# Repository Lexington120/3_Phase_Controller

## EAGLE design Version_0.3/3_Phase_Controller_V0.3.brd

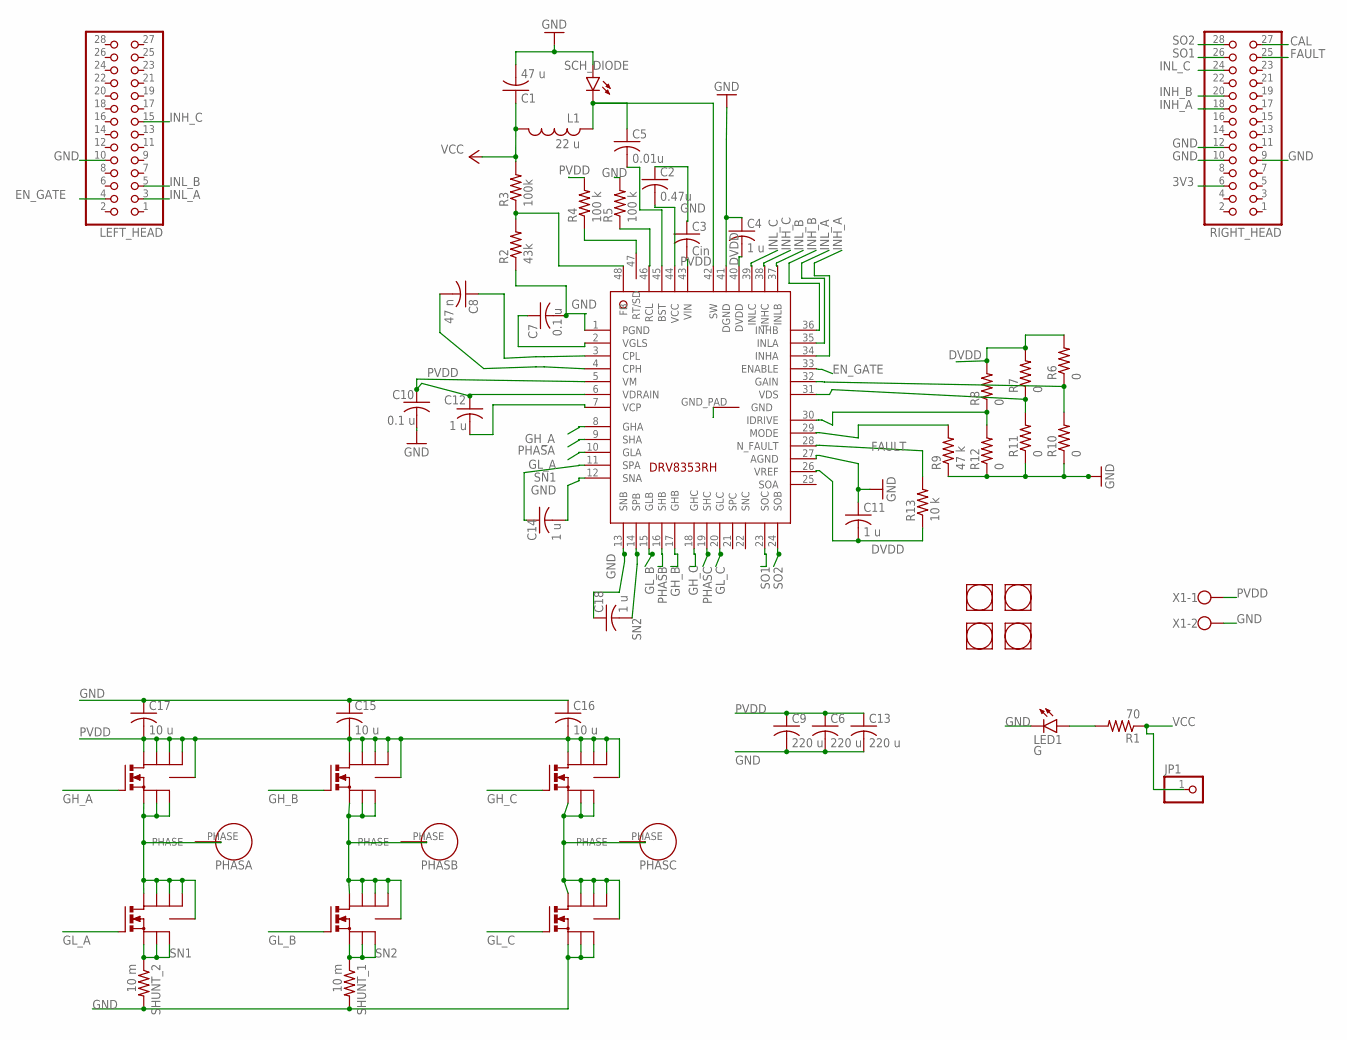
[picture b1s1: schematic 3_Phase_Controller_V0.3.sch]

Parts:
A_H: SIR178DP; POWERPAK_SO-8_SINGLE
A_L: SIR178DP; POWERPAK_SO-8_SINGLE
B_H: SIR178DP; POWERPAK_SO-8_SINGLE
B_L: SIR178DP; POWERPAK_SO-8_SINGLE
C1: 47 u; C025-024X044
C2: 0.47u; C0805
C3: Cin; C0805
C4, C11, C12, C14, C18: 1 u; C0805
C5: 0.01u; C0805
C6, C9, C13: 220 u; C050-045X075
C7, C10: 0.1 u; C0805
C8: 47 n; C0805
C15, C16, C17: 10 u; C1206
C_H: SIR178DP; POWERPAK_SO-8_SINGLE
C_L: SIR178DP; POWERPAK_SO-8_SINGLE
JP1: PINHD-1X1; 1X01
L1: 22 u; L3225M
LED1: G; SML0805
LEFT_HEAD: PINHD-2X14; 2X14
PHASE_A: PHASE_HOLE_V_0.2; HOLE_V_0.2
PHASE_B: PHASE_HOLE_V_0.2; HOLE_V_0.2
PHASE_C: PHASE_HOLE_V_0.2; HOLE_V_0.2
R1: 70; R0805
R2: 43k; R0603
R3: 100k; R0603
R4, R5: 100 k; R0805
R6, R7, R8, R10, R11, R12: 0; R0603
R9: 47 k; R0603
R13: 10 k; R0603
RIGHT_HEAD: PINHD-2X14; 2X14
SCH_DIODE: LEDCHIP-LED0805; CHIP-LED0805
SHUNT_1, SHUNT_2: 10 m; R2512
U$1, U$2, U$4, U$5: STANDOFF
U$3: DRV8353RH; VQFN-RGZ0048A
X1: W237-102

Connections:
3V3: RIGHT_HEAD.6
CAL: RIGHT_HEAD.27
DVDD: C4.2, C11.2, R6.2, R7.2, R8.2, R13.1, U$3.26 (VREF), U$3.40 (DVDD)
EN_GATE: LEFT_HEAD.4, U$3.33 (ENABLE)
FAULT: R13.2, RIGHT_HEAD.25, U$3.28 (N_FAULT)
GH_A: A_H.GATE (G), U$3.8 (GHA)
GH_B: B_H.GATE (G), U$3.17 (GHB)
GH_C: C_H.GATE (G), U$3.18 (GHC)
GL_A: A_L.GATE (G), U$3.10 (GLA)
GL_B: B_L.GATE (G), U$3.15 (GLB)
GL_C: C_L.GATE (G), U$3.20 (GLC)
GND: C1.2, C2.1, C3.1, C4.1, C6.2, C7.2, C9.2, C10.2, C11.1, C13.2, C14.2, C15.1, C16.1, C17.1, C18.1, C_L.S_1 (S), C_L.S_2 (S1), C_L.S_3 (S2), LED1.C, LEFT_HEAD.10, R2.1, R5.2, R9.1, R10.1, R11.1, R12.1, RIGHT_HEAD.9, RIGHT_HEAD.10, RIGHT_HEAD.12, SCH_DIODE.A, SHUNT_1.2, SHUNT_2.2, U$3.1 (PGND), U$3.12 (SNA), U$3.13 (SNB), U$3.27 (AGND), U$3.41 (DGND), U$3.GND_PAD (GND), X1.2
INH_A: RIGHT_HEAD.18, U$3.34 (INHA)
INH_B: RIGHT_HEAD.20, U$3.36 (INHB)
INH_C: LEFT_HEAD.15, U$3.38 (INHC)
INL_A: LEFT_HEAD.3, U$3.35 (INLA)
INL_B: LEFT_HEAD.5, U$3.37 (INLB)
INL_C: RIGHT_HEAD.24, U$3.39 (INLC)
unnamed: LED1.A, R1.2
unnamed: R6.1, R10.2, U$3.32 (GAIN)
unnamed: R2.2, R3.1, U$3.48 (FB)
unnamed: R7.1, R11.2, U$3.31 (VDS)
unnamed: C5.2, U$3.45 (BST)
unnamed: R8.1, R12.2, U$3.30 (IDRIVE)
unnamed: R9.2, U$3.29 (MODE)
unnamed: C2.2, U$3.44 (VCC)
unnamed: C12.2, U$3.7 (VCP)
unnamed: C7.1, U$3.2 (VGLS)
unnamed: R5.1, U$3.46 (RCL)
unnamed: R4.1, U$3.47 (RT/SD)
unnamed: C5.1, L1.2, SCH_DIODE.C, U$3.42 (SW)
unnamed: C8.2, U$3.4 (CPH)
unnamed: C8.1, U$3.3 (CPL)
PHASA: A_H.S_1 (S), A_H.S_2 (S1), A_H.S_3 (S2), A_L.D_1 (D), A_L.D_2 (D1), A_L.D_3 (D2), A_L.D_4 (D3), A_L.THRM (THERMAL), PHASE_A.PHASE, U$3.9 (SHA)
PHASB: B_H.S_1 (S), B_H.S_2 (S1), B_H.S_3 (S2), B_L.D_1 (D), B_L.D_2 (D1), B_L.D_3 (D2), B_L.D_4 (D3), B_L.THRM (THERMAL), PHASE_B.PHASE, U$3.16 (SHB)
PHASC: C_H.S_1 (S), C_H.S_2 (S1), C_H.S_3 (S2), C_L.D_1 (D), C_L.D_2 (D1), C_L.D_3 (D2), C_L.D_4 (D3), C_L.THRM (THERMAL), PHASE_C.PHASE, U$3.19 (SHC)
PVDD: A_H.D_1 (D), A_H.D_2 (D1), A_H.D_3 (D2), A_H.D_4 (D3), A_H.THRM (THERMAL), B_H.D_1 (D), B_H.D_2 (D1), B_H.D_3 (D2), B_H.D_4 (D3), B_H.THRM (THERMAL), C3.2, C6.1, C9.1, C10.1, C12.1, C13.1, C15.2, C16.2, C17.2, C_H.D_1 (D), C_H.D_2 (D1), C_H.D_3 (D2), C_H.D_4 (D3), C_H.THRM (THERMAL), R4.2, U$3.5 (VM), U$3.6 (VDRAIN), U$3.43 (VIN), X1.1
SN1: A_L.S_1 (S), A_L.S_2 (S1), A_L.S_3 (S2), C14.1, SHUNT_2.1, U$3.11 (SPA)
SN2: B_L.S_1 (S), B_L.S_2 (S1), B_L.S_3 (S2), C18.2, SHUNT_1.1, U$3.14 (SPB)
SO1: RIGHT_HEAD.26, U$3.23 (SOC)
SO2: RIGHT_HEAD.28, U$3.24 (SOB)
VCC: C1.1, JP1.1, L1.1, R1.1, R3.2

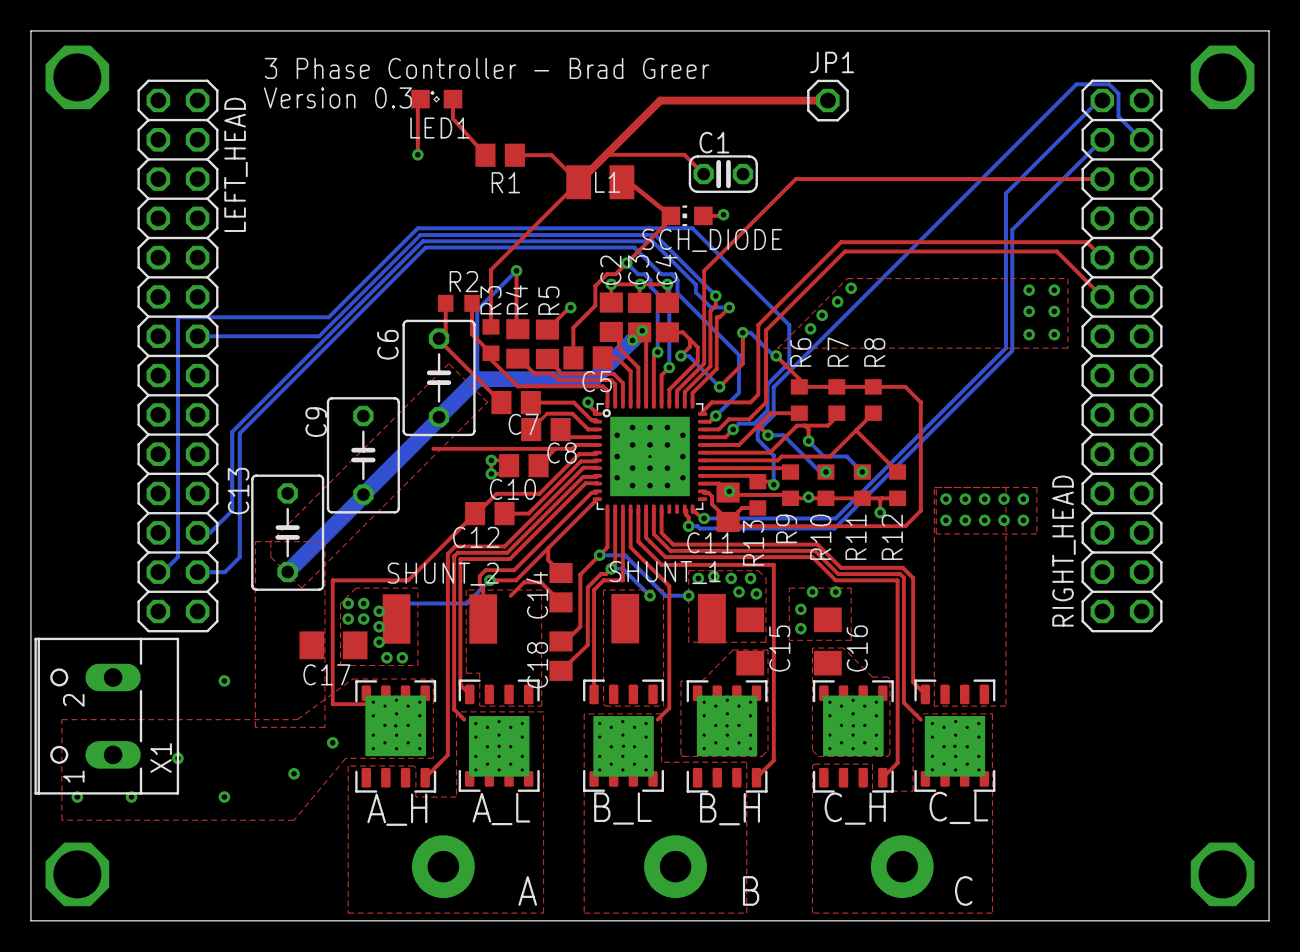
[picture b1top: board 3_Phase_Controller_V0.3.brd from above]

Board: 2 copper layers, 80.0 x 57.5 mm, 54 parts (0 on the bottom side), 40 nets.

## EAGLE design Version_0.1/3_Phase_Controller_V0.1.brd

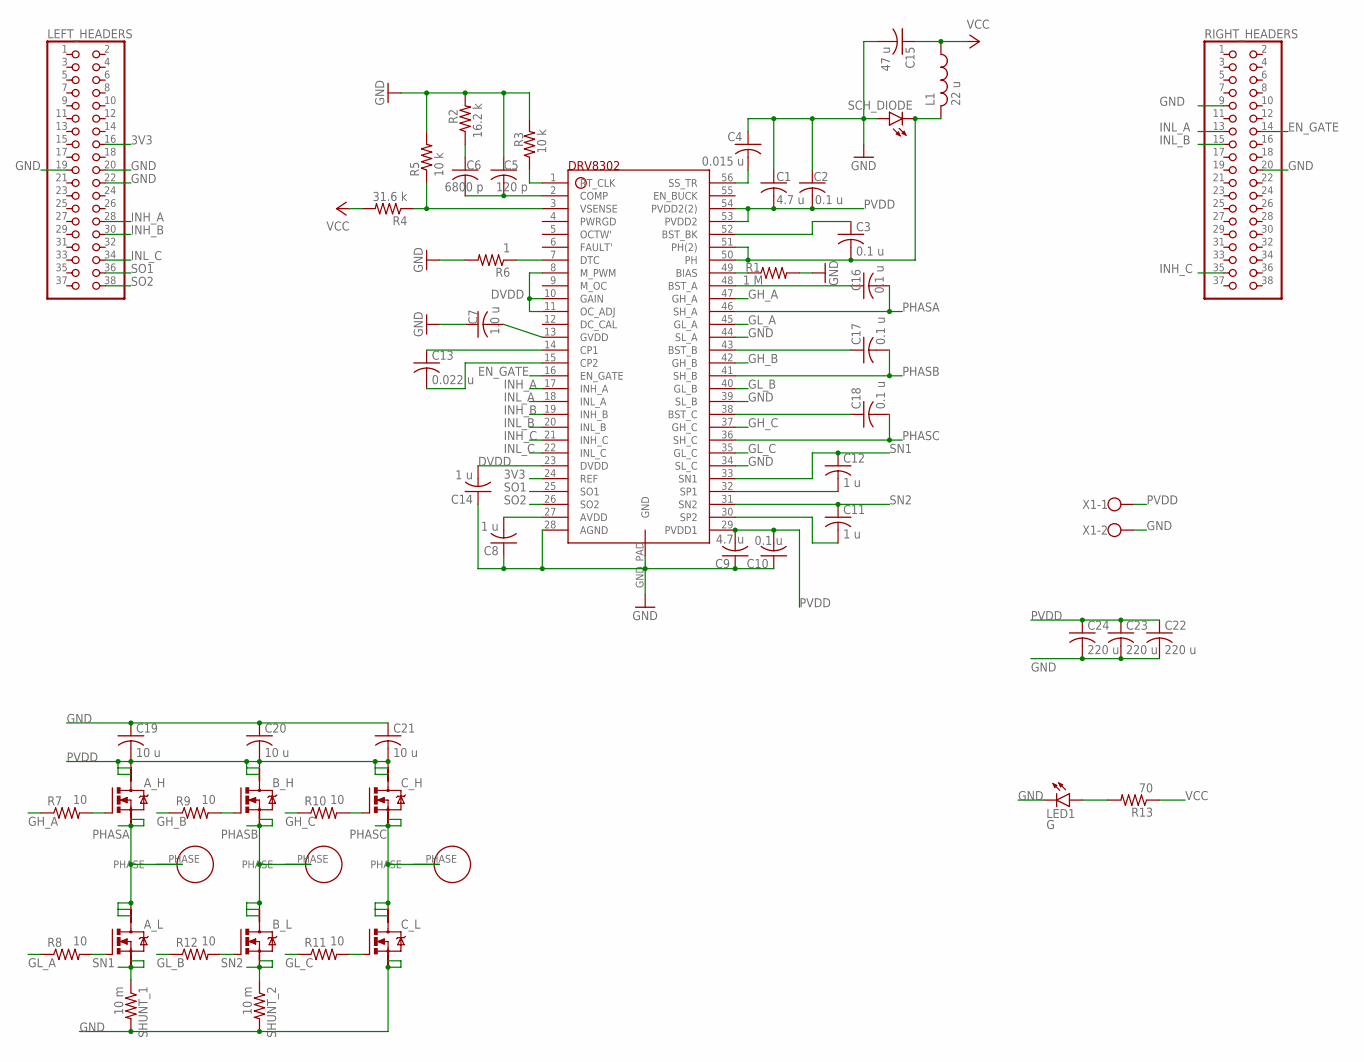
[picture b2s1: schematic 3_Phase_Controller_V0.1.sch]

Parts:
A: PHASE_HOLE; HOLE
A_H: N-MOSFET-SO8S; SO-08
A_L: N-MOSFET-SO8S; SO-08
B: PHASE_HOLE; HOLE
B_H: N-MOSFET-SO8S; SO-08
B_L: N-MOSFET-SO8S; SO-08
C: PHASE_HOLE; HOLE
C1, C9: 4.7 u; C0805
C2, C3, C10, C16, C17, C18: 0.1 u; C0805
C4: 0.015 u; C0805
C5: 120 p; C0805
C6: 6800 p; C0805
C7: 1.0 u; C0805
C8, C11, C12, C14: 1 u; C0805
C13: 0.022 u; C0805
C15: 47 u; C025-024X044
C19, C20, C21: 10 u; C1206
C22, C23, C24: 220 u; C050-045X075
C_H: N-MOSFET-SO8S; SO-08
C_L: N-MOSFET-SO8S; SO-08
DRV8302: DRV8302HTSSOP_56; HTSSOP56DFD
L1: 22 u; L3225M
LED1: G; SML0805
LEFT_HEADERS: F_PINH 2X19; 2X19
R1: 1 M; R0805
R2: 16.2 k; R0805
R3, R5: 10 k; R0805
R4: 31.6 k; R0805
R6: 1; R0805
R7, R8, R9, R10, R11, R12: 10; R0805
R13: 70; R0805
RIGHT_HEADERS: F_PINH 2X19; 2X19
SCH_DIODE: LEDCHIP-LED0805; CHIP-LED0805
SHUNT_1, SHUNT_2: 10 m; R2512
X1: W237-102

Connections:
3V3: DRV8302.24 (REF), LEFT_HEADERS.16
DVDD: C14.2, DRV8302.8 (M_PWM), DRV8302.10 (GAIN), DRV8302.11 (OC_ADJ), DRV8302.23 (DVDD)
EN_GATE: DRV8302.16 (EN_GATE), RIGHT_HEADERS.14
GH_A: DRV8302.47 (GH_A), R7.1
GH_B: DRV8302.42 (GH_B), R9.1
GH_C: DRV8302.37 (GH_C), R10.1
GL_A: DRV8302.45 (GL_A), R8.1
GL_B: DRV8302.40 (GL_B), R12.1
GL_C: DRV8302.35 (GL_C), R11.1
GND: C1.1, C2.1, C4.1, C5.1, C7.1, C8.1, C9.1, C10.1, C14.1, C15.2, C19.1, C20.1, C21.1, C22.2, C23.2, C24.2, C_L.1 (S), C_L.2 (S), DRV8302.28 (AGND), DRV8302.34 (SL_C), DRV8302.39 (SL_B), DRV8302.44 (SL_A), DRV8302.GND_PAD (GND), LED1.C, LEFT_HEADERS.19, LEFT_HEADERS.20, LEFT_HEADERS.22, R1.2, R2.2, R3.2, R5.2, R6.2, RIGHT_HEADERS.9, RIGHT_HEADERS.20, SCH_DIODE.A, SHUNT_1.2, SHUNT_2.2, X1.2
INH_A: DRV8302.17 (INH_A), LEFT_HEADERS.28
INH_B: DRV8302.19 (INH_B), LEFT_HEADERS.30
INH_C: DRV8302.21 (INH_C), RIGHT_HEADERS.35
INL_A: DRV8302.18 (INL_A), RIGHT_HEADERS.13
INL_B: DRV8302.20 (INL_B), RIGHT_HEADERS.15
INL_C: DRV8302.22 (INL_C), LEFT_HEADERS.34
unnamed: LED1.A, R13.2
unnamed: C3.2, DRV8302.50 (PH), DRV8302.51 (PH(2)), L1.2, SCH_DIODE.C
unnamed: C3.1, DRV8302.52 (BST_BK)
unnamed: C4.2, DRV8302.56 (SS_TR)
unnamed: C11.2, DRV8302.30 (SP2)
unnamed: C12.2, DRV8302.32 (SP1)
unnamed: DRV8302.7 (DTC), R6.1
unnamed: C7.2, DRV8302.13 (GVDD)
unnamed: C8.2, DRV8302.27 (AVDD)
unnamed: DRV8302.49 (BIAS), R1.1
unnamed: DRV8302.1 (RT_CLK), R3.1
unnamed: C5.2, C6.2, DRV8302.2 (COMP)
unnamed: C6.1, R2.1
unnamed: DRV8302.3 (VSENSE), R4.1, R5.1
unnamed: C13.1, DRV8302.14 (CP1)
unnamed: C13.2, DRV8302.15 (CP2)
unnamed: A_H.4 (G), R7.2
unnamed: C17.1, DRV8302.43 (BST_B)
unnamed: A_L.4 (G), R8.2
unnamed: B_H.4 (G), R9.2
unnamed: C_H.4 (G), R10.2
unnamed: C18.1, DRV8302.38 (BST_C)
unnamed: C_L.4 (G), R11.2
unnamed: C16.1, DRV8302.48 (BST_A)
unnamed: B_L.4 (G), R12.2
PHASA: A.PHASE, A_H.1 (S), A_H.2 (S), A_L.5 (D), A_L.6 (D), A_L.7 (D), C16.2, DRV8302.46 (SH_A)
PHASB: B.PHASE, B_H.1 (S), B_H.2 (S), B_L.5 (D), B_L.6 (D), B_L.7 (D), C17.2, DRV8302.41 (SH_B)
PHASC: C.PHASE, C18.2, C_H.1 (S), C_H.2 (S), C_L.5 (D), C_L.6 (D), C_L.7 (D), DRV8302.36 (SH_C)
PVDD: A_H.5 (D), A_H.6 (D), A_H.7 (D), B_H.5 (D), B_H.6 (D), B_H.7 (D), C1.2, C2.2, C9.2, C10.2, C19.2, C20.2, C21.2, C22.1, C23.1, C24.1, C_H.5 (D), C_H.6 (D), C_H.7 (D), DRV8302.29 (PVDD1), DRV8302.53 (PVDD2), DRV8302.54 (PVDD2(2)), X1.1
SN1: A_L.1 (S), A_L.2 (S), C12.1, DRV8302.33 (SN1), SHUNT_1.1
SN2: B_L.1 (S), B_L.2 (S), C11.1, DRV8302.31 (SN2), SHUNT_2.1
SO1: DRV8302.25 (SO1), LEFT_HEADERS.36
SO2: DRV8302.26 (SO2), LEFT_HEADERS.38
VCC: C15.1, L1.1, R4.2, R13.1

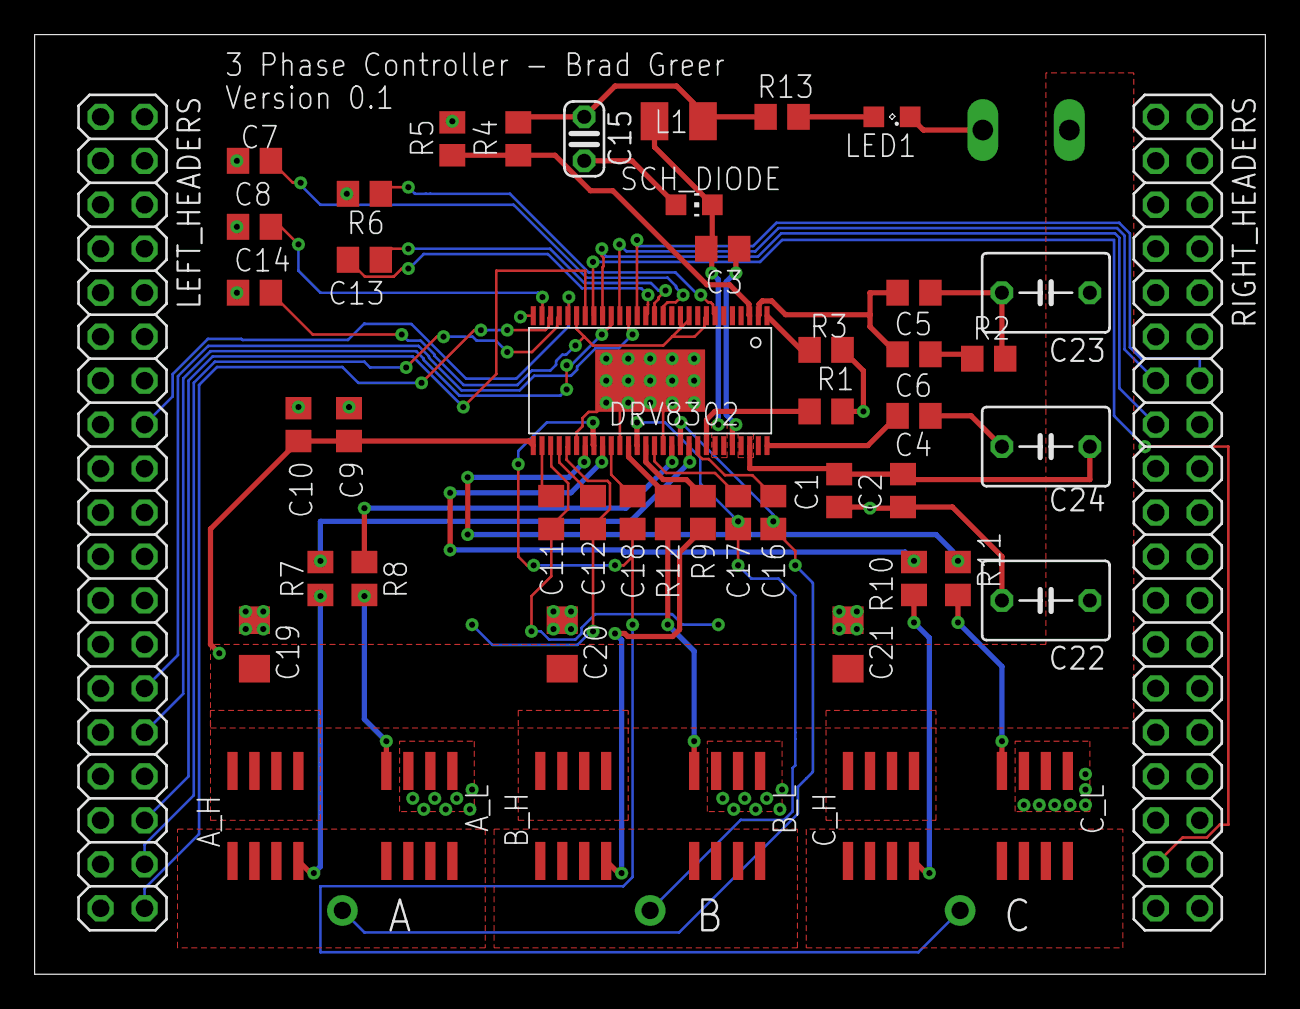
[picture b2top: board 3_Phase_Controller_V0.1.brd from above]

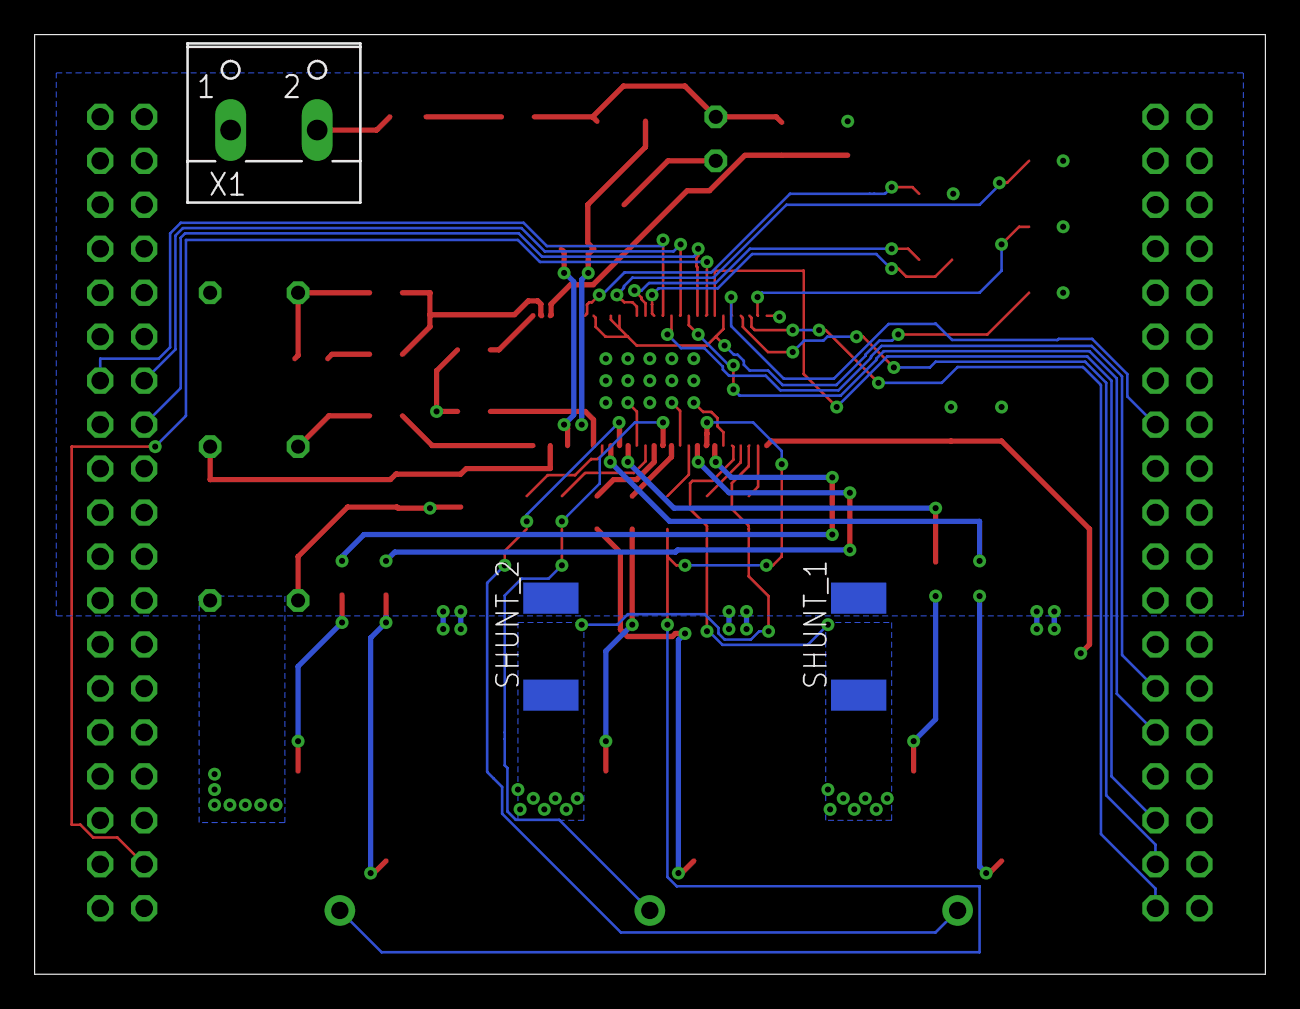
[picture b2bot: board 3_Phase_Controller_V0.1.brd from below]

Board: 2 copper layers, 71.1 x 54.3 mm, 55 parts (3 on the bottom side), 50 nets.

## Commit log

2021-04-24 Placeholder file
2021-04-24 First commit from bash! Includes all current files.
2021-04-24 Work that is not mine removed for the most part.
2021-04-25 Testing with adding a .gitignore file.
2021-04-25 Seeing if the .gitignore works on test~.txt.
2021-04-25 Testing creating files on Github
2021-04-25 Modified .gitignore file test.
2021-06-27 V0.2 finished; starting V0.3
2021-06-27 .gitignore fix
2021-06-27 cleaning up
2021-07-01 Testing ignore
2021-07-01 Testing ignore_2
2021-07-02 Version 0.3 finished and ordered.
2021-07-03 V0.3 BOM added
2021-07-09 Soldermask error fixed
